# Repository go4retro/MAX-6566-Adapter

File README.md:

# MAX-6566-Adapter
Minimized layout of Christian Forstreuter's 6566->6567 Adapter

All credit for the design goes to Christian.  I simply re-laid out the board to be as small as possible and ordered a few to have stock for those needing to swap out their 6566 IC.

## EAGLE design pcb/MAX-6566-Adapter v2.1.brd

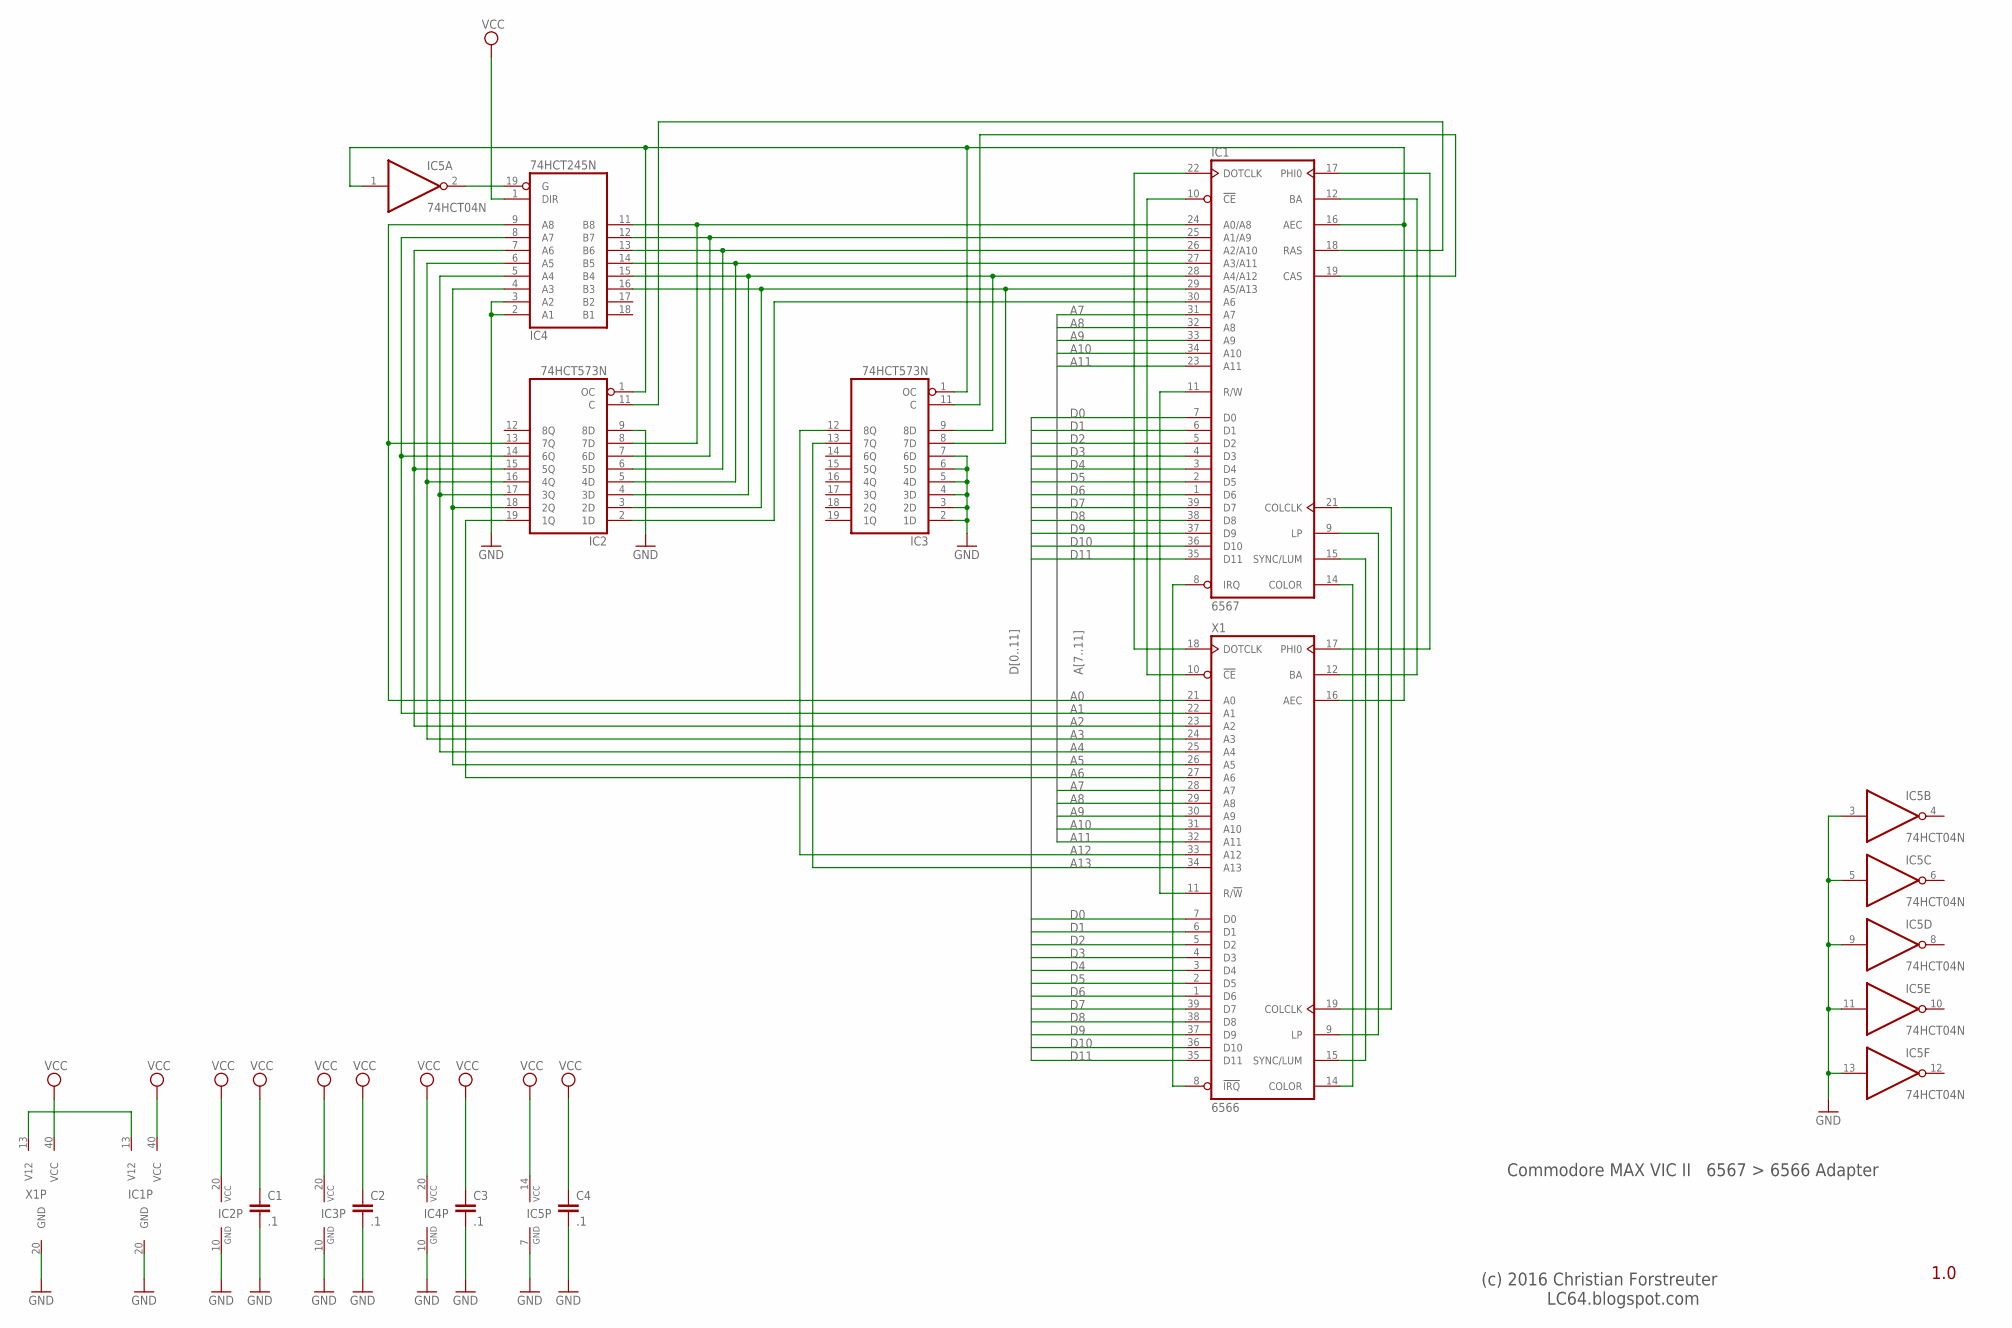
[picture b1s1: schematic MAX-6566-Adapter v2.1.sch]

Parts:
C1, C2, C3, C4: .1; C025-024X044
IC1: 6567; DIL40-ROUNDPAD
IC2, IC3: 74HCT573N; 74XX-EU_DIL20
IC4: 74HCT245N; 74XX-EU_DIL20
IC5: 74HCT04N; 74XX-EU_DIL14
X1: 6566; DIL40-ROUNDPAD

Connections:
A0: IC2.13 (7Q), IC4.9 (A8), X1.21 (A0)
A1: IC2.14 (6Q), IC4.8 (A7), X1.22 (A1)
A2: IC2.15 (5Q), IC4.7 (A6), X1.23 (A2)
A3: IC2.16 (4Q), IC4.6 (A5), X1.24 (A3)
A4: IC2.17 (3Q), IC4.5 (A4), X1.25 (A4)
A5: IC2.18 (2Q), IC4.4 (A3), X1.26 (A5)
A6: IC2.19 (1Q), X1.27 (A6)
A7: IC1.31 (A7), X1.28 (A7)
A8: IC1.32 (A8), X1.29 (A8)
A9: IC1.33 (A9), X1.30 (A9)
A10: IC1.34 (A10), X1.31 (A10)
A11: IC1.23 (A11), X1.32 (A11)
A12: IC3.12 (8Q), X1.33 (A12)
A13: IC3.13 (7Q), X1.34 (A13)
AEC: IC1.16 (AEC), IC2.1 (OC), IC3.1 (OC), IC5.1 (I), X1.16 (AEC)
D0: IC1.7 (D0), X1.7 (D0)
D1: IC1.6 (D1), X1.6 (D1)
D2: IC1.5 (D2), X1.5 (D2)
D3: IC1.4 (D3), X1.4 (D3)
D4: IC1.3 (D4), X1.3 (D4)
D5: IC1.2 (D5), X1.2 (D5)
D6: IC1.1 (D6), X1.1 (D6)
D7: IC1.39 (D7), X1.39 (D7)
D8: IC1.38 (D8), X1.38 (D8)
D9: IC1.37 (D9), X1.37 (D9)
D10: IC1.36 (D10), X1.36 (D10)
D11: IC1.35 (D11), X1.35 (D11)
GND: C1.2, C2.2, C3.2, C4.2, IC1.20 (GND), IC2.9 (8D), IC2.10 (GND), IC3.2 (1D), IC3.3 (2D), IC3.4 (3D), IC3.5 (4D), IC3.6 (5D), IC3.7 (6D), IC3.10 (GND), IC4.2 (A1), IC4.3 (A2), IC4.10 (GND), IC5.3 (I), IC5.5 (I), IC5.7 (GND), IC5.9 (I), IC5.11 (I), IC5.13 (I), X1.20 (GND)
unnamed: IC1.9 (LP), X1.9 (LP)
unnamed: IC1.12 (BA), X1.12 (BA)
unnamed: IC1.17 (PHI0), X1.17 (PHI0)
unnamed: IC1.15 (SYNC/LUM), X1.15 (SYNC/LUM)
unnamed: IC1.14 (COLOR), X1.14 (COLOR)
unnamed: IC1.22 (DOTCLK), X1.18 (DOTCLK)
unnamed: IC1.21 (COLCLK), X1.19 (COLCLK)
unnamed: IC1.11 (R/W), X1.11 (R/!W)
unnamed: IC1.8 (IRQ), X1.8 (!IRQ)
unnamed: IC1.10 (!CE), X1.10 (!CE)
unnamed: IC4.19 (G), IC5.2 (O)
unnamed: IC1.24 (A0/A8), IC2.8 (7D), IC4.11 (B8)
unnamed: IC1.18 (RAS), IC2.11 (C)
unnamed: IC1.19 (CAS), IC3.11 (C)
unnamed: IC1.13 (V12), X1.13 (V12)
unnamed: IC1.26 (A2/A10), IC2.6 (5D), IC4.13 (B6)
unnamed: IC1.27 (A3/A11), IC2.5 (4D), IC4.14 (B5)
unnamed: IC1.28 (A4/A12), IC2.4 (3D), IC3.9 (8D), IC4.15 (B4)
unnamed: IC1.29 (A5/A13), IC2.3 (2D), IC3.8 (7D), IC4.16 (B3)
unnamed: IC1.30 (A6), IC2.2 (1D)
unnamed: IC1.25 (A1/A9), IC2.7 (6D), IC4.12 (B7)
VCC: C1.1, C2.1, C3.1, C4.1, IC1.40 (VCC), IC2.20 (VCC), IC3.20 (VCC), IC4.1 (DIR), IC4.20 (VCC), IC5.14 (VCC), X1.40 (VCC)

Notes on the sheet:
Commodore MAX VIC II 6567 > 6566 Adapter
(c) 2016 Christian Forstreuter LC64.blogspot.com
1.0

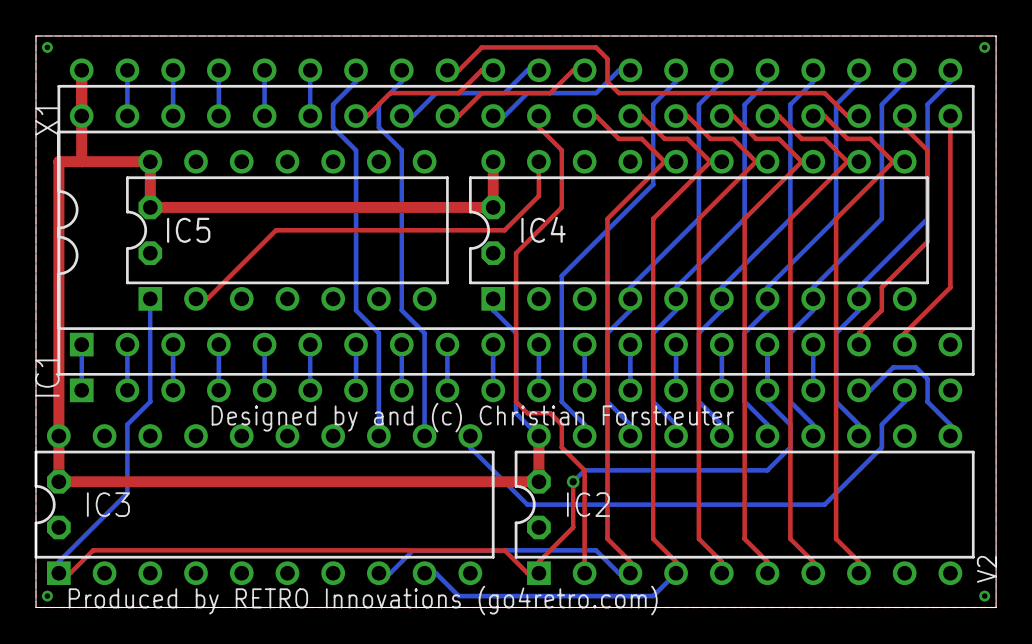
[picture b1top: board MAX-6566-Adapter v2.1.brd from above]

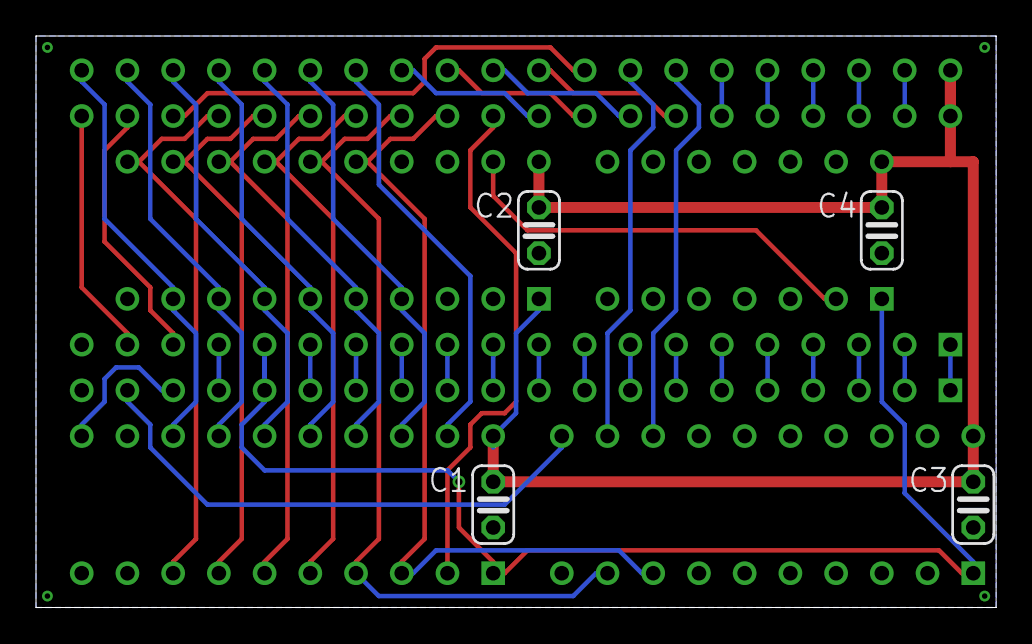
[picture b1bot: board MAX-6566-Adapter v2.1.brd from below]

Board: 2 copper layers, 53.3 x 31.7 mm, 10 parts (4 on the bottom side), 50 nets.
